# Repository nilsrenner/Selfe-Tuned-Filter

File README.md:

# Self-Tuned-Filter

## Kontext
Diese Bachelorarbeit wurde im März 2026 an der **Hochschule Bremen** (Fakultät 4: Elektrotechnik und Informatik) abgegeben. Ziel war das Design, die Simulation und die messtechnische Verifizierung eines analogen, selbsteinstellenden Filters auf Basis eines spannungsgesteuerten Biquad-Filters.

## Projektbeschreibung
Das System passt seine Resonanzfrequenz eigenständig an die anliegende Eingangsfrequenz an. Die zentrale Steuerung übernimmt ein **Raspberry Pi Pico 2 W**, der als digitale Schnittstelle dient.

* **Wissenschaftlicher Kern:** Eigenständige Herleitung und Verifikation der Gleichungen zur Resonanzfrequenz (Korrektur fehlerhafter Angaben im ASLK-PRO Manual).
* **Hardware:** Entwicklung eines PCB für die Umsetzung des Self-Tuned Systems.
* **Software:** MicroPython-Skript zur Steuerung des Filters über eine webbasierte Oberfläche. Nulldurchgangszähler für die Eingangsfrequenzdetektion.
* **Ergebnis:** Für frequenzgebende Widerstände von 1 kΩ wurde die Funktionalität im Bereich von ca. **240 Hz bis über 12 kHz** nachgewiesen. 

---

## Struktur des Repositoriums
Die Quelldaten sind wie folgt strukturiert:

| Ordner / Datei | Inhalt |
| :--- | :--- |
| **`001_Simulation_und_Schaltungsentwurf`** | Datenblätter, Simulationen und PCB-Entwürfe (V1 & V2). |
| **`002_3D_Modell`** | 3D-Modell der PCB-Halterung für den Versuchsaufbau. |
| **`003_Messdaten`** | Rohdaten der Messungen (Oszilloskop und Red Pitaya). |
| **`004_Code`** | MicroPython-Skripts für den Raspberry Pi Pico 2 W. |
| **`005_Dokumentation`** | LaTeX-Quellcode der Arbeit. |
| **`Bachelor_Thesis_Renner_2026.pdf`** | Die Bachelorarbeit in digitaler Form. |

---

## Autor & Prüfer
* **Autor:** Nils Renner
* **Prüfer:** Prof. Dr.-Ing. Mirco Meiners & Prof. Dr. Sören Peik

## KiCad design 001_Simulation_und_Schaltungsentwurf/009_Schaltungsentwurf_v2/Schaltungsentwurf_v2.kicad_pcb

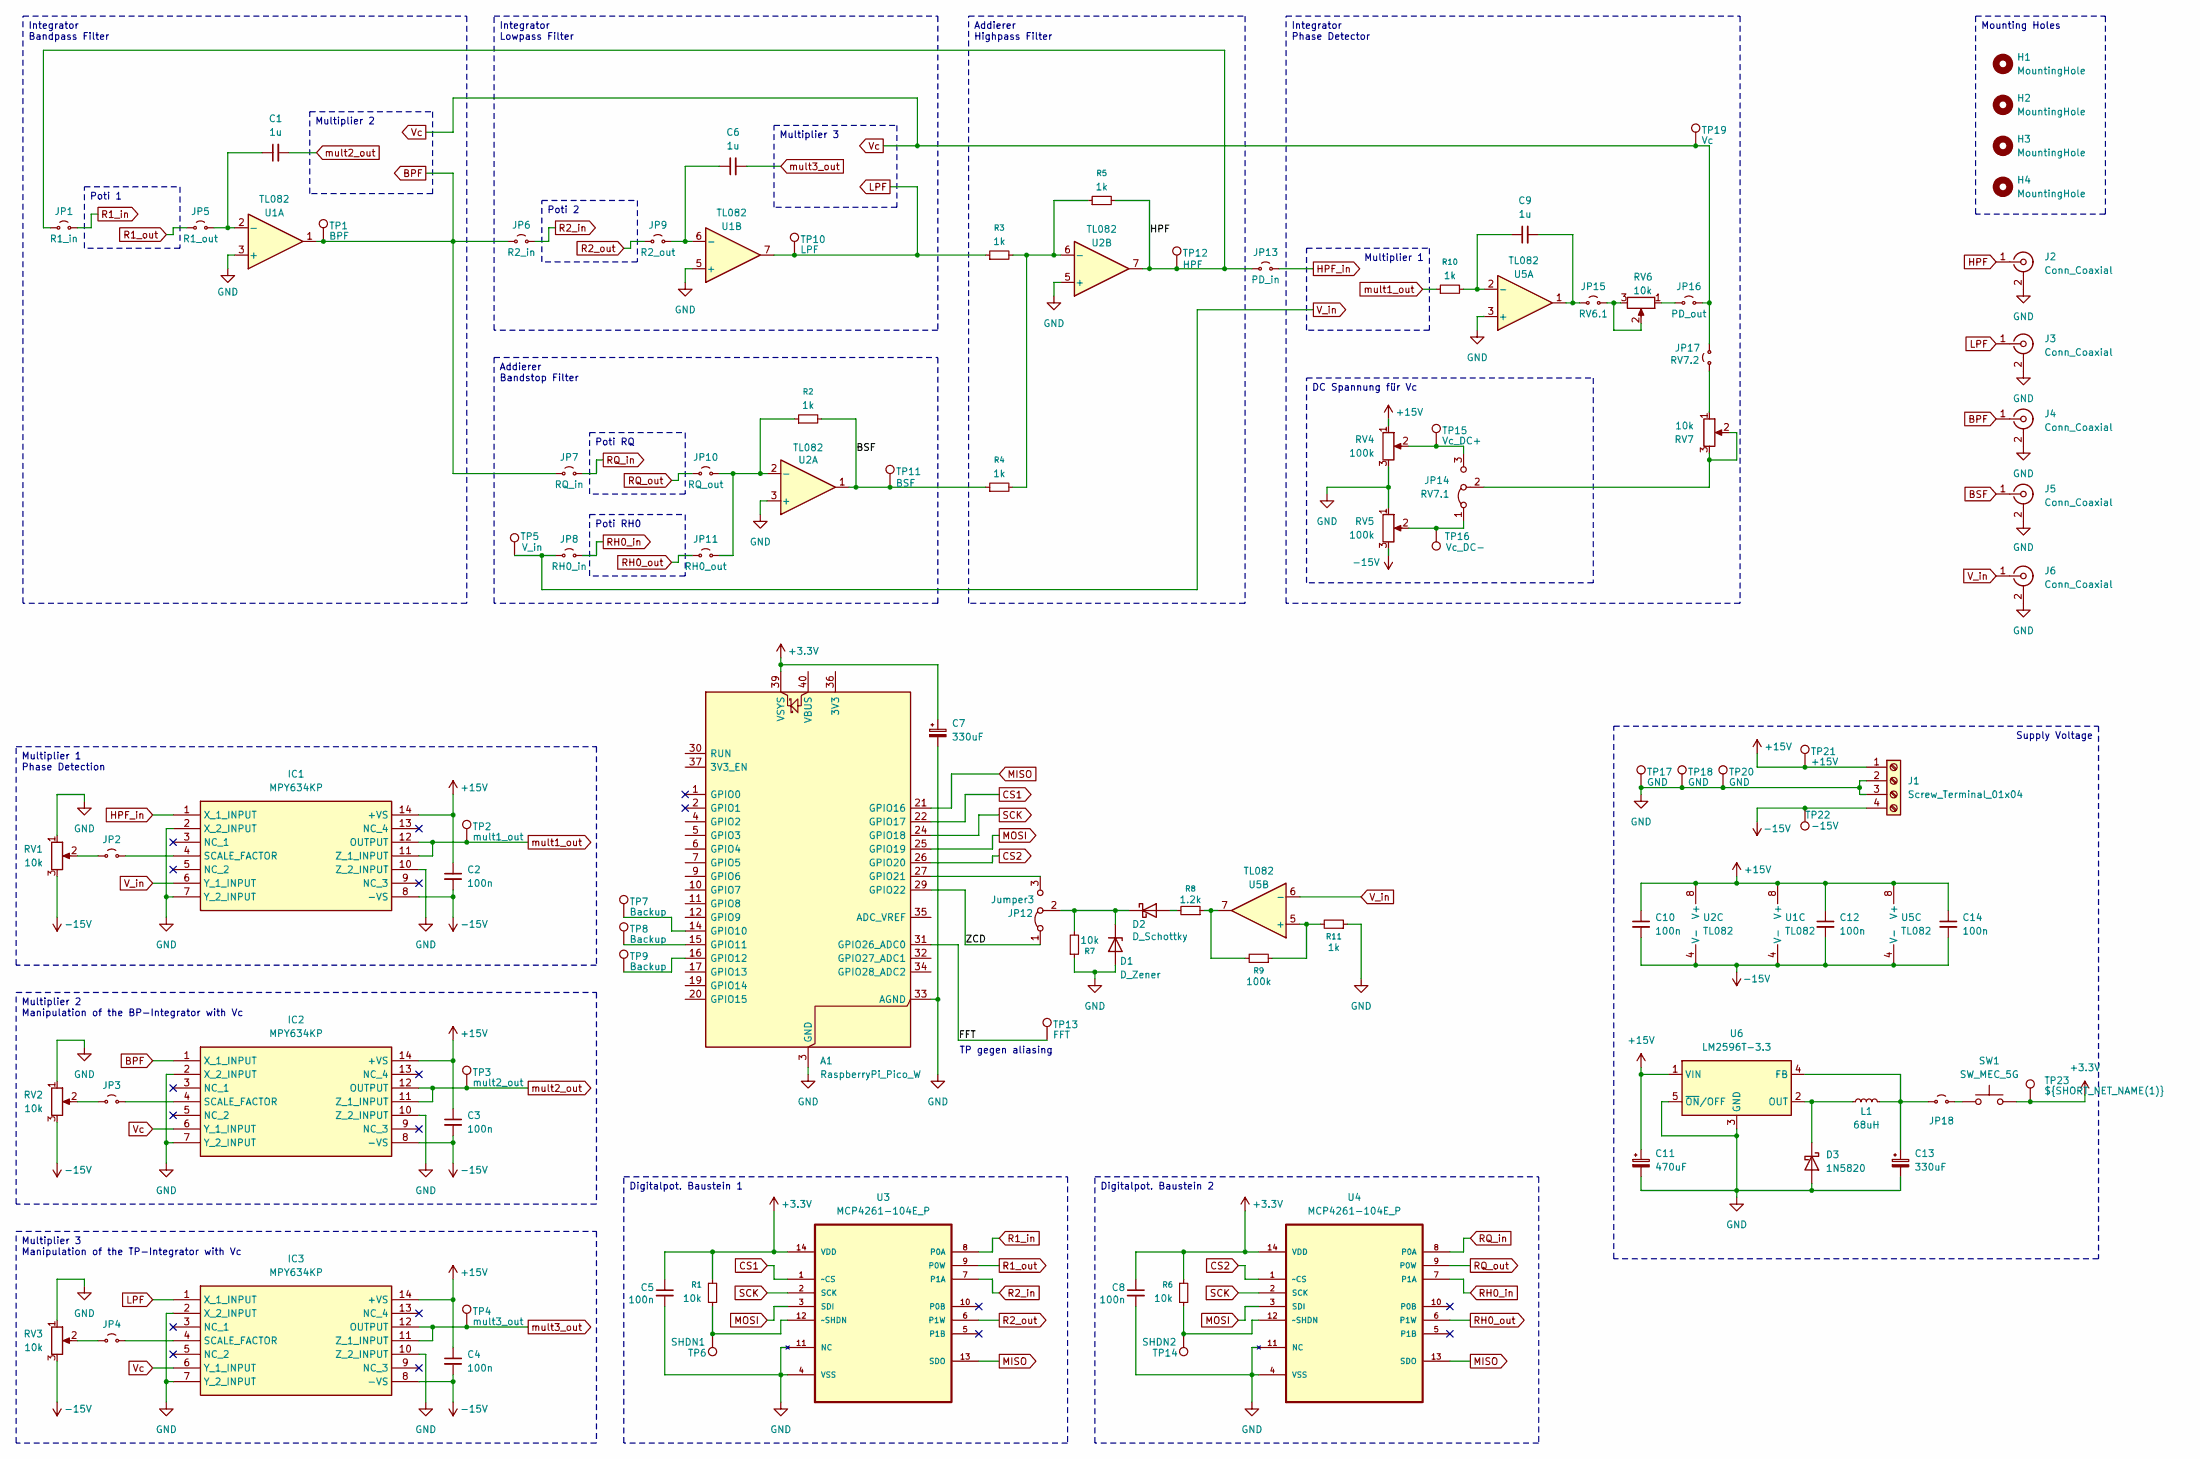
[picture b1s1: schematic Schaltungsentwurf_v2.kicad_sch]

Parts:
A1: RaspberryPi_Pico_W; RaspberryPi_Pico_W_THT
C1, C6, C9: 1u; 100nF
C2, C3, C4, C5, C8, C10, C12, C14: 100n; 100nF
C7, C13: 330uF; C_Radial_D10.0mm_H16.0mm_P5.00mm
C11: 470uF; C_Radial_D10.0mm_H16.0mm_P5.00mm
D1: D_Zener; 1N4001
D2: D_Schottky; 1N4001
D3: 1N5820; D_DO-27_P15.24mm_Horizontal
H1, H2, H3, H4: MountingHole; MountingHole_2.2mm_M2_DIN965
IC1, IC2, IC3: MPY634KP; DIP_14; Mouser Part Number 595-MPY634KP
J1: Screw_Terminal_01x04; Terminal 4 Pol
J2, J3, J4, J5, J6: Conn_Coaxial; BNC Edge Mount
JP1: R1_in; Connector 2 Pin 2.54mm
JP2, JP3, JP4, JP18: Connector 2 Pin 2.54mm
JP5: R1_out; Connector 2 Pin 2.54mm
JP6: R2_in; Connector 2 Pin 2.54mm
JP7: RQ_in; Connector 2 Pin 2.54mm
JP8: RH0_in; Connector 2 Pin 2.54mm
JP9: R2_out; Connector 2 Pin 2.54mm
JP10: RQ_out; Connector 2 Pin 2.54mm
JP11: RH0_out; Connector 2 Pin 2.54mm
JP12: Jumper3; Connector 3 Pin 2,54mm
JP13: PD_in; Connector 2 Pin 2.54mm
JP14: RV7.1; Connector 3 Pin 2,54mm
JP15: RV6.1; Connector 2 Pin 2.54mm
JP16: PD_out; Connector 2 Pin 2.54mm
JP17: RV7.2; Connector 2 Pin 2.54mm
L1: 68uH; L_Radial_D8.7mm_P5.00mm_Fastron_07HCP
R1, R6, R7: 10k; Resistor
R2, R3, R4, R5, R10, R11: 1k; Resistor
R8: 1.2k; Resistor
R9: 100k; Resistor
RV1, RV2, RV3, RV6, RV7: 10k; Potentiometer_Bourns_3296Y_Vertical
RV4, RV5: 100k; Potentiometer_Bourns_3296Y_Vertical
SW1: SW_MEC_5G; SW_DIP_SPSTx03_Piano_10.8x9.18mm_W7.62mm_P2.54mm
TP1: BPF; TestPoint; Mouser Part Number 534-5015
TP2: mult1_out; TestPoint; Mouser Part Number 534-5015
TP3: mult2_out; TestPoint; Mouser Part Number 534-5015
TP4: mult3_out; TestPoint; Mouser Part Number 534-5015
TP5: V_in; TestPoint; Mouser Part Number 534-5015
TP6: SHDN1; TestPoint; Mouser Part Number 534-5015
TP7, TP8, TP9: Backup; TestPoint; Mouser Part Number 534-5015
TP10: LPF; TestPoint; Mouser Part Number 534-5015
TP11: BSF; TestPoint; Mouser Part Number 534-5015
TP12: HPF; TestPoint; Mouser Part Number 534-5015
TP13: FFT; TestPoint; Mouser Part Number 534-5015
TP14: SHDN2; TestPoint; Mouser Part Number 534-5015
TP15: Vc_DC+; TestPoint; Mouser Part Number 534-5015
TP16: Vc_DC-; TestPoint; Mouser Part Number 534-5015
TP17, TP18, TP20: GND; TestPoint; Mouser Part Number 534-5015
TP19: Vc; TestPoint; Mouser Part Number 534-5015
TP21: +15V; TestPoint; Mouser Part Number 534-5015
TP22: -15V; TestPoint; Mouser Part Number 534-5015
TP23: ${SHORT_NET_NAME(1)}; TestPoint
U1, U2, U5: TL082; DIP_8
U3, U4: MCP4261-104E_P; DIP_14; MPN MCP4261-104E/P
U6: LM2596T-3.3; TO-220-5_P3.4x3.7mm_StaggerOdd_Lead3.8mm_Vertical

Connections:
+3.3V: A1.39 (VSYS), C5.1, C7.1, C8.1, R1.1, R6.1, SW1.3 (B), SW1.4 (B), TP23.1, U3.14 (VDD), U4.14 (VDD)
+15V: C2.1, C3.1, C4.1, C10.1, C11.1, C12.1, C14.1, IC1.14 (+VS), IC2.14 (+VS), IC3.14 (+VS), J1.1, RV4.1, TP21.1, U1.8 (V+), U2.8 (V+), U5.8 (V+), U6.1 (VIN)
-15V: C2.2, C3.2, C4.2, C10.2, C12.2, C14.2, IC1.8 (-VS), IC2.8 (-VS), IC3.8 (-VS), J1.4, RV1.3, RV2.3, RV3.3, RV5.3, TP22.1, U1.4 (V-), U2.4 (V-), U5.4 (V-)
/FFT: A1.31 (GPIO26_ADC0), TP13.1
/ZCD: A1.29 (GPIO22), JP12.1 (A)
BPF: IC2.1 (X_1_INPUT), J4.1 (In), JP6.1 (A), JP7.1 (A), TP1.1, U1.1
BSF: J5.1 (In), R2.2, R4.1, TP11.1, U2.1
CS1: A1.22 (GPIO17), U3.1 (~CS)
CS2: A1.26 (GPIO20), U4.1 (~CS)
GND: A1.3 (GND), A1.8 (GND), A1.13 (GND), A1.18 (GND), A1.23 (GND), A1.28 (GND), A1.33 (AGND), A1.38 (GND), C5.2, C7.2, C8.2, C11.2, C13.2, D1.2 (A), D3.2 (A), IC1.2 (X_2_INPUT), IC1.7 (Y_2_INPUT), IC1.10 (Z_2_INPUT), IC2.2 (X_2_INPUT), IC2.7 (Y_2_INPUT), IC2.10 (Z_2_INPUT), IC3.2 (X_2_INPUT), IC3.7 (Y_2_INPUT), IC3.10 (Z_2_INPUT), J1.2, J1.3, J2.2 (Ext), J3.2 (Ext), J4.2 (Ext), J5.2 (Ext), J6.2 (Ext), R7.1, R11.1, RV1.1, RV2.1, RV3.1, RV4.3, RV5.1, TP17.1, TP18.1, TP20.1, U1.3 (+), U1.5 (+), U2.3 (+), U2.5 (+), U3.4 (VSS), U3.11 (NC), U4.4 (VSS), U4.11 (NC), U5.3 (+), U6.3 (GND), U6.5 (~ON/OFF)
HPF: J2.1 (In), JP1.1 (A), JP13.1 (A), R5.2, TP12.1, U2.7
HPF_in: IC1.1 (X_1_INPUT), JP13.2 (B)
LPF: IC3.1 (X_1_INPUT), J3.1 (In), R3.1, TP10.1, U1.7
MISO: A1.21 (GPIO16), U3.13 (SDO), U4.13 (SDO)
MOSI: A1.25 (GPIO19), U3.3 (SDI), U4.3 (SDI)
unnamed: A1.14 (GPIO10), TP7.1
unnamed: A1.15 (GPIO11), TP8.1
unnamed: A1.16 (GPIO12), TP9.1
unnamed: A1.27 (GPIO21), JP12.3 (B)
unnamed: D1.1 (K), D2.1 (K), JP12.2 (C), R7.2
unnamed: D2.2 (A), R8.2
unnamed: D3.1 (K), L1.1, U6.2 (OUT)
unnamed: IC1.4 (SCALE_FACTOR), JP2.2 (B)
unnamed: IC2.4 (SCALE_FACTOR), JP3.2 (B)
unnamed: IC3.4 (SCALE_FACTOR), JP4.2 (B)
unnamed: JP2.1 (A), RV1.2
unnamed: JP3.1 (A), RV2.2
unnamed: JP4.1 (A), RV3.2
unnamed: C1.1, JP5.2 (B), U1.2 (-)
unnamed: C6.1, JP9.2 (B), U1.6 (-)
unnamed: JP10.2 (B), JP11.2 (B), R2.1, U2.2 (-)
unnamed: JP14.1 (A), RV5.2, TP16.1
unnamed: JP14.3 (B), RV4.2, TP15.1
unnamed: JP14.2 (C), RV7.2, RV7.3
unnamed: C9.2, JP15.1 (A), U5.1
unnamed: JP15.2 (B), RV6.2, RV6.3
unnamed: JP16.1 (A), RV6.1
unnamed: JP17.1 (A), RV7.1
unnamed: C13.1, JP18.1 (A), L1.2, U6.4 (FB)
unnamed: JP18.2 (B), SW1.1 (A), SW1.2 (A)
unnamed: R8.1, R9.2, U5.7
unnamed: R3.2, R4.2, R5.1, U2.6 (-)
unnamed: R1.2, TP6.1, U3.12 (~SHDN)
unnamed: R6.2, TP14.1, U4.12 (~SHDN)
unnamed: C9.1, R10.2, U5.2 (-)
unnamed: R9.1, R11.2, U5.5 (+)
R1_in: JP1.2 (B), U3.8 (P0A)
R1_out: JP5.1 (A), U3.9 (P0W)
R2_in: JP6.2 (B), U3.7 (P1A)
R2_out: JP9.1 (A), U3.6 (P1W)
RH0_in: JP8.2 (B), U4.7 (P1A)
RH0_out: JP11.1 (A), U4.6 (P1W)
RQ_in: JP7.2 (B), U4.8 (P0A)
RQ_out: JP10.1 (A), U4.9 (P0W)
SCK: A1.24 (GPIO18), U3.2 (SCK), U4.2 (SCK)
V_in: IC1.6 (Y_1_INPUT), J6.1 (In), JP8.1 (A), TP5.1, U5.6 (-)
Vc: IC2.6 (Y_1_INPUT), IC3.6 (Y_1_INPUT), JP16.2 (B), JP17.2 (B), TP19.1
mult1_out: IC1.11 (Z_1_INPUT), IC1.12 (OUTPUT), R10.1, TP2.1
mult2_out: C1.2, IC2.11 (Z_1_INPUT), IC2.12 (OUTPUT), TP3.1
mult3_out: C6.2, IC3.11 (Z_1_INPUT), IC3.12 (OUTPUT), TP4.1

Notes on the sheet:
TP gegen aliasing
Poti 2
Supply Voltage
Digitalpot. Baustein 1
Poti RH0
Multiplier 2
Multiplier 2 Manipulation of the BP-Integrator with Vc
Multiplier 1 Phase Detection
Mounting Holes
Poti 1
Multiplier 3 Manipulation of the TP-Integrator with Vc
Digitalpot. Baustein 2
Addierer Highpass Filter
Integrator Bandpass Filter
DC Spannung für Vc
Multiplier 3
Multiplier 1
Addierer Bandstop Filter
Integrator Lowpass Filter
Poti RQ
Integrator Phase Detector

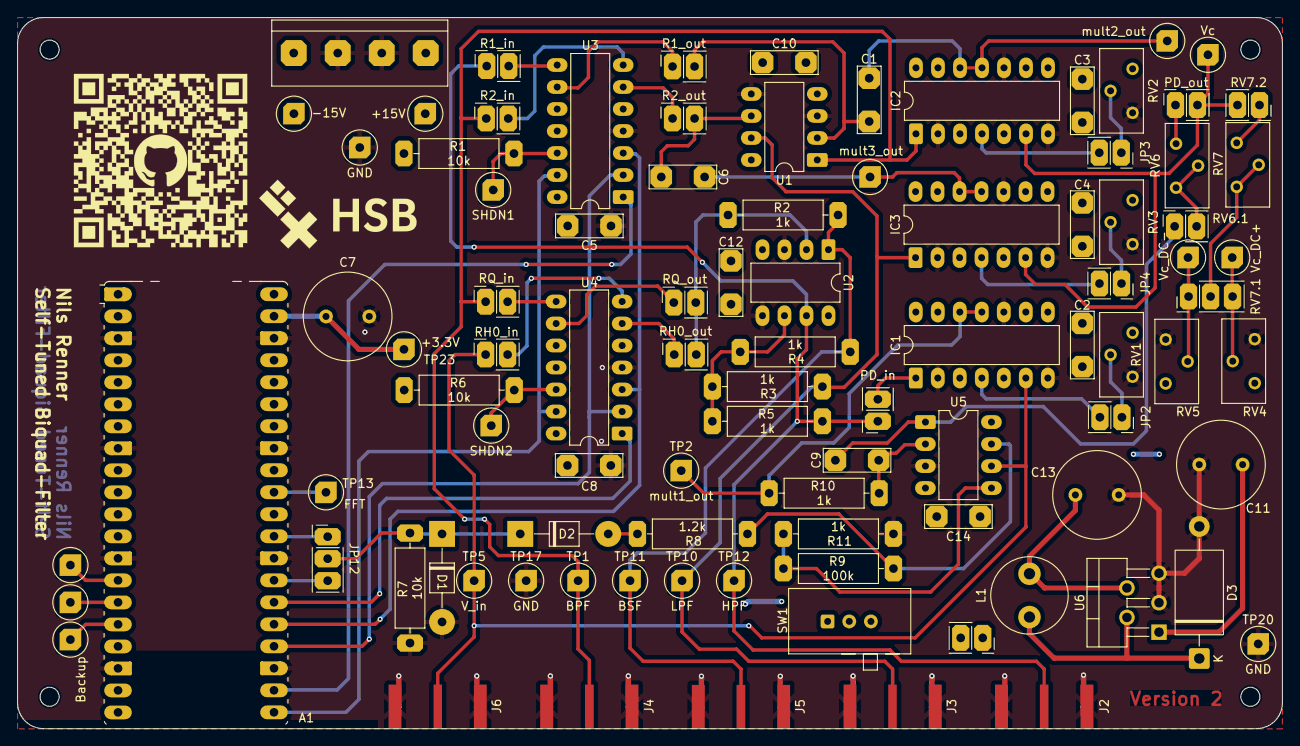
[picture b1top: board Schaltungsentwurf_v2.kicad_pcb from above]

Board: 4 copper layers, 146.0 x 82.1 mm, 100 parts (1 on the bottom side), 60 nets.

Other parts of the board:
Ref**: Val**; git_qr
Ref**#2: Val**; logo_nils

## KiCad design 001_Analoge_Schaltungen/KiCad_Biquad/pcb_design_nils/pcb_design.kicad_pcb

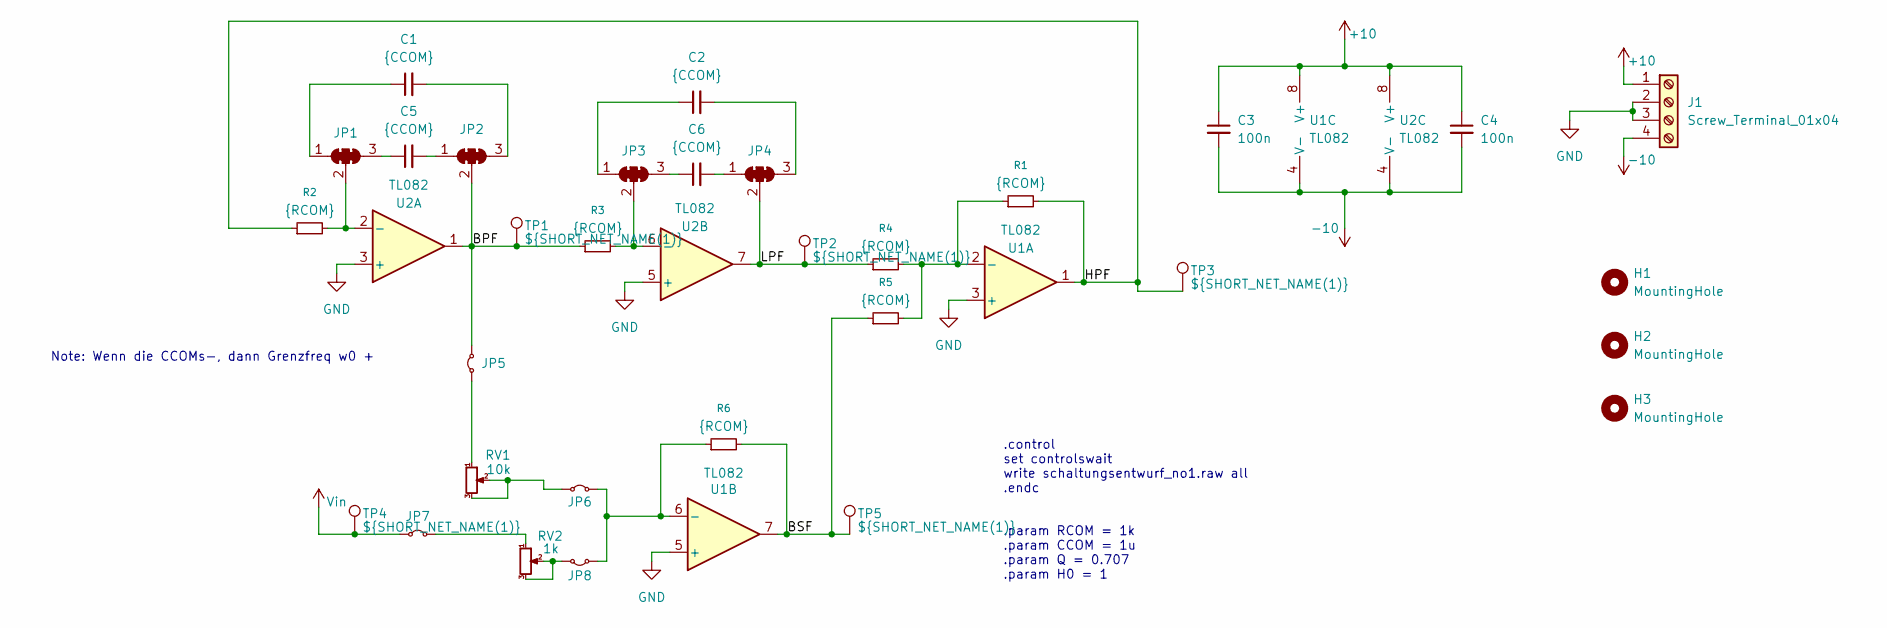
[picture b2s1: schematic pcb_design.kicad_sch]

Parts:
C1, C2: {CCOM}; 1-10uF
C3, C4: 100n; 100nF
C5, C6: {CCOM}; 100nF
H1, H2, H3: MountingHole; MountingHole_2.2mm_M2_DIN965
J1: Screw_Terminal_01x04; Terminal 4 Pol
JP1, JP2, JP3, JP4: SolderJumper_3_Bridged123; Connector 3 Pin 2,54mm
JP5, JP6, JP7, JP8: Jumper_2_Small_Bridged; Connector 2 Pin 2.54mm
R1, R2, R3, R4, R5, R6: {RCOM}; Resistor
RV1: 10k; Potentiometer_Bourns_3266W_Vertical
RV2: 1k; Potentiometer_Bourns_3266W_Vertical
TP1, TP2, TP3, TP4, TP5: ${SHORT_NET_NAME(1)}; TestPoint; Mouser Part Number 534-5015
U1, U2: TL082; DIP 8

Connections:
+10: C3.1, C4.1, J1.1, U1.8 (V+), U2.8 (V+)
-10: C3.2, C4.2, J1.4, U1.4 (V-), U2.4 (V-)
/BPF: JP2.2 (C), JP5.2 (B), R3.1, TP1.1, U2.1
/BSF: R5.1, R6.2, TP5.1, U1.7
/HPF: R1.2, R2.1, TP3.1, U1.1
/LPF: JP4.2 (C), R4.1, TP2.1, U2.7
GND: J1.2, J1.3, U1.3 (+), U1.5 (+), U2.3 (+), U2.5 (+)
unnamed: C1.1, JP1.1 (A)
unnamed: C5.1, JP1.3 (B)
unnamed: JP1.2 (C), R2.2, U2.2 (-)
unnamed: C5.2, JP2.1 (A)
unnamed: C1.2, JP2.3 (B)
unnamed: C2.1, JP3.1 (A)
unnamed: C6.1, JP3.3 (B)
unnamed: JP3.2 (C), R3.2, U2.6 (-)
unnamed: C6.2, JP4.1 (A)
unnamed: C2.2, JP4.3 (B)
unnamed: JP5.1 (A), RV1.1
unnamed: JP6.1 (A), RV1.2, RV1.3
unnamed: JP6.2 (B), JP8.1 (A), R6.1, U1.6 (-)
unnamed: JP7.2 (B), RV2.1
unnamed: JP8.2 (B), RV2.2, RV2.3
unnamed: R1.1, R4.2, R5.2, U1.2 (-)
Vin: JP7.1 (A), TP4.1

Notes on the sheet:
.param RCOM = 1k .param CCOM = 1u .param Q = 0.707 .param H0 = 1
Note: Wenn die CCOMs-, dann Grenzfreq w0 +
.control set controlswait write schaltungsentwurf_no1.raw all .endc

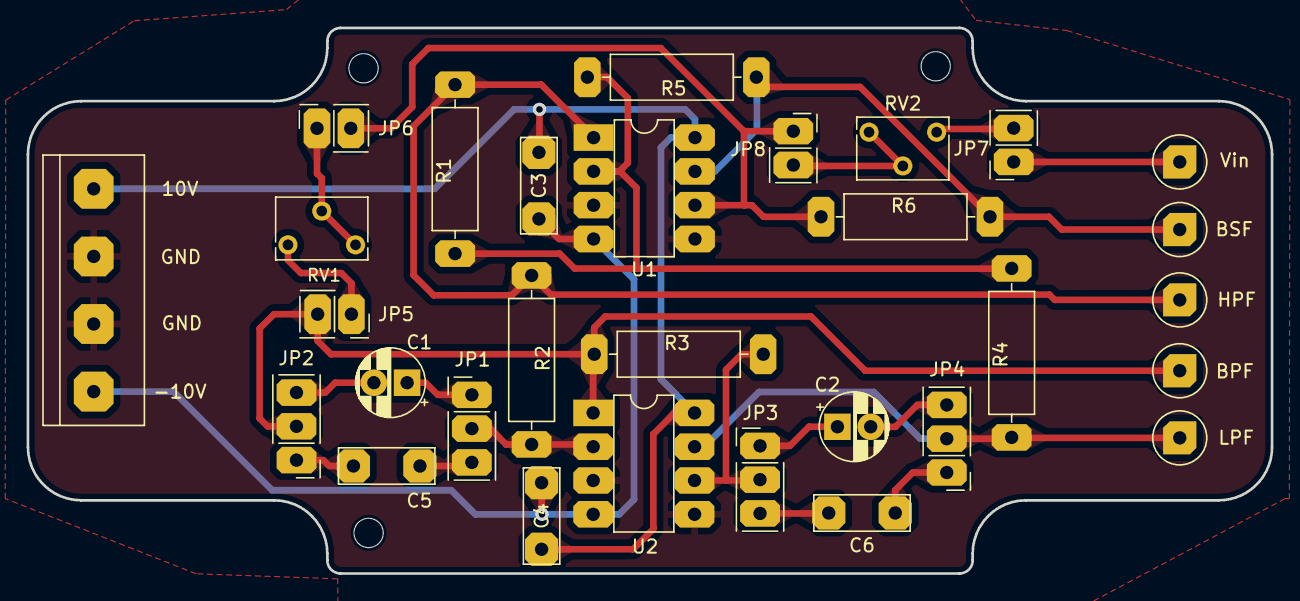
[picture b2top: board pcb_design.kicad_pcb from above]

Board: 2 copper layers, 93.5 x 41.0 mm, 34 parts (0 on the bottom side), 24 nets.

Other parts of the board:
H4: MountingHole; MountingHole_2.2mm_M2_DIN965

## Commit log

2025-09-09 Kopie der Auto Messwertaufnahme erstellt
2025-09-16 Simulation muss aufgrund von neuistallation von KiCad neu gemaucht werden, 1/2 fertig
2025-09-20 chore:add untracked files
2025-09-20 chore: aufgeräumt
2025-09-20 githubpage
2025-09-20 .nojekyll
2026-02-01 pcb_version_2, new pcb holder
2026-02-07 PD-Vermessung und Sprungantwortsimulation
2026-02-11 Durchführung von Simulationen am Gesamtsystem
2026-02-12 Simualtion 2
2026-02-15 Weiterarbeit an UI und Nulldurchgangszähler
2026-02-19 Added CITATION
2026-02-23 aktueller Stand
2026-02-24 Ordnerstruktur verbessert
2026-02-24 Cleaned PDFLaTeX run
2026-02-24 pgf plots
2026-02-25 Update README with project details and structure
    Added detailed project context, description, repository structure, and author information.
2026-02-27 Hinzufügen der PDF
